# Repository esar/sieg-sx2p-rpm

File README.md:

# sieg-sx2p-rpm
SIEG SX2P Mini Mill RPM and Feed Display

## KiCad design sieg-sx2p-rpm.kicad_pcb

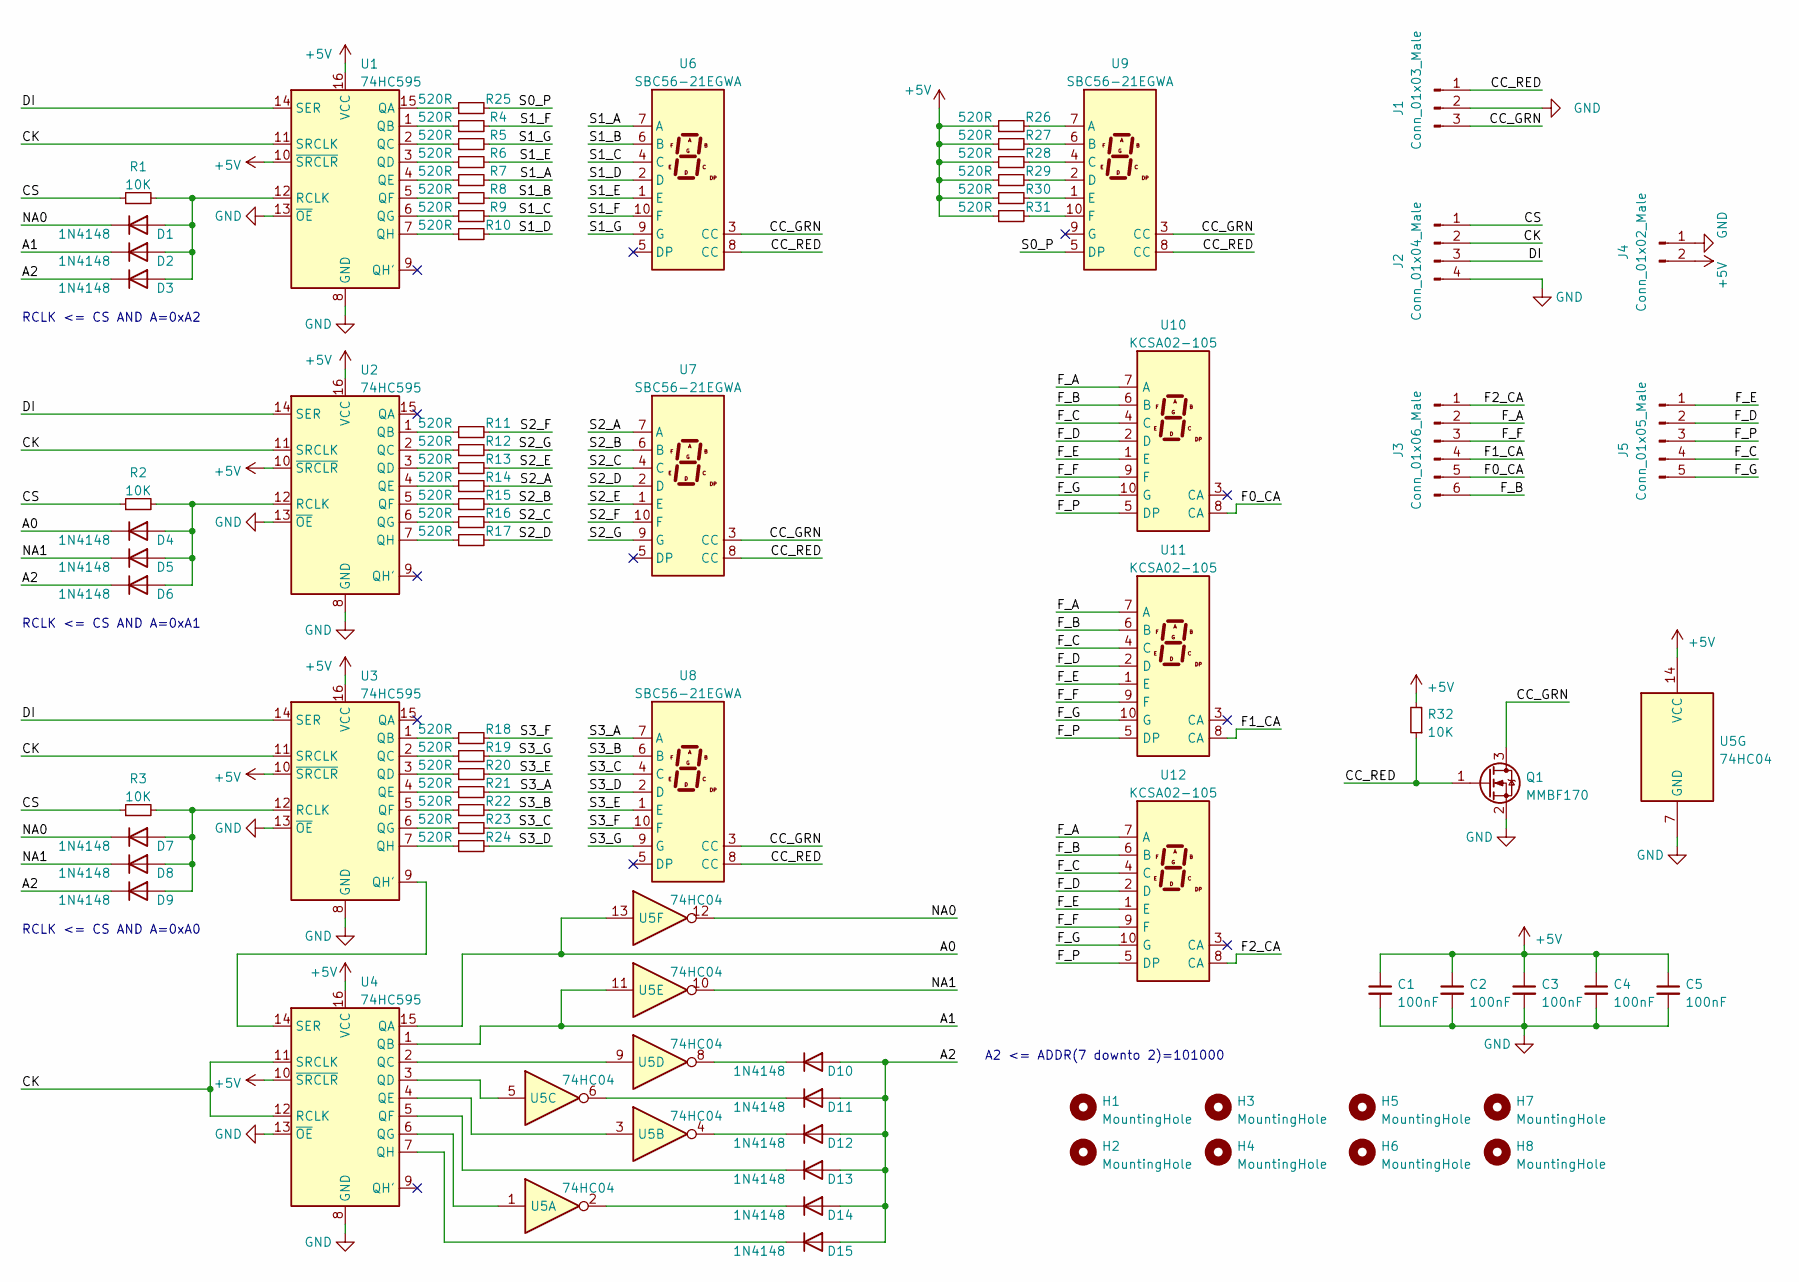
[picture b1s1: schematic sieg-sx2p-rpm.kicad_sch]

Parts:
C1, C2, C3, C4, C5: 100nF; C_0603_1608Metric
D1, D2, D3, D4, D5, D6, D7, D8, D9, D10, D11, D12, D13, D14, D15: 1N4148; D_SOD-323
H1, H2, H3, H4, H5, H6, H7, H8: MountingHole; MountingHole_3mm
J1: Conn_01x03_Male; JST_XH_B3B-XH-A_1x03_P2.50mm_Vertical
J2: Conn_01x04_Male; JST_XH_B4B-XH-A_1x04_P2.50mm_Vertical
J3: Conn_01x06_Male; JST_XH_B6B-XH-A_1x06_P2.50mm_Vertical
J4: Conn_01x02_Male; JST_XH_B2B-XH-A_1x02_P2.50mm_Vertical
J5: Conn_01x05_Male; JST_XH_B5B-XH-A_1x05_P2.50mm_Vertical
Q1: MMBF170; SOT-23
R1, R2, R3, R32: 10K; R_0603_1608Metric
R4, R5, R6, R7, R8, R9, R10, R11, R12, R13, R14, R15, R16, R17, R18, R19, R20, R21, R22, R23, R24, R25, R26, R27, R28, R29, R30, R31: 520R; R_0603_1608Metric
U1, U2, U3, U4: 74HC595; DIP-16_W7.62mm
U5: 74HC04; DIP-14_W7.62mm
U6, U7, U8, U9: SBC56-21EGWA; D1X8K
U10, U11, U12: KCSA02-105; D1X8K

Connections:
+5V: C1.1, C2.1, C3.1, C4.1, C5.1, J4.2, R26.1, R27.1, R28.1, R29.1, R30.1, R31.1, R32.2, U1.10 (~SRCLR), U1.16 (VCC), U2.10 (~SRCLR), U2.16 (VCC), U3.10 (~SRCLR), U3.16 (VCC), U4.10 (~SRCLR), U4.16 (VCC), U5.14 (VCC)
/A0: D4.1 (K), U4.15 (QA), U5.13
/A1: D2.1 (K), U4.1 (QB), U5.11
/A2: D3.1 (K), D6.1 (K), D9.1 (K), D10.2 (A), D11.2 (A), D12.2 (A), D13.2 (A), D14.2 (A), D15.2 (A)
/CC_GRN: J1.3, Q1.3 (D), U6.3 (CC), U7.3 (CC), U8.3 (CC), U9.3 (CC)
/CC_RED: J1.1, Q1.1 (G), R32.1, U6.8 (CC), U7.8 (CC), U8.8 (CC), U9.8 (CC)
/CK: J2.2, U1.11 (SRCLK), U2.11 (SRCLK), U3.11 (SRCLK), U4.11 (SRCLK), U4.12 (RCLK)
/CS: J2.1, R1.1, R2.1, R3.1
/DI: J2.3, U1.14 (SER), U2.14 (SER), U3.14 (SER)
/F0_CA: J3.5, U10.8 (CA)
/F1_CA: J3.4, U11.8 (CA)
/F2_CA: J3.1, U12.8 (CA)
/F_A: J3.2, U10.7 (A), U11.7 (A), U12.7 (A)
/F_B: J3.6, U10.6 (B), U11.6 (B), U12.6 (B)
/F_C: J5.4, U10.4 (C), U11.4 (C), U12.4 (C)
/F_D: J5.2, U10.2 (D), U11.2 (D), U12.2 (D)
/F_E: J5.1, U10.1 (E), U11.1 (E), U12.1 (E)
/F_F: J3.3, U10.9 (F), U11.9 (F), U12.9 (F)
/F_G: J5.5, U10.10 (G), U11.10 (G), U12.10 (G)
/F_P: J5.3, U10.5 (DP), U11.5 (DP), U12.5 (DP)
/NA0: D1.1 (K), D7.1 (K), U5.12
/NA1: D5.1 (K), D8.1 (K), U5.10
/S0_P: R25.2, U9.5 (DP)
/S1_A: R7.2, U6.7 (A)
/S1_B: R8.2, U6.6 (B)
/S1_C: R9.2, U6.4 (C)
/S1_D: R10.2, U6.2 (D)
/S1_E: R6.2, U6.1 (E)
/S1_F: R4.2, U6.10 (F)
/S1_G: R5.2, U6.9 (G)
/S2_A: R14.2, U7.7 (A)
/S2_B: R15.2, U7.6 (B)
/S2_C: R16.2, U7.4 (C)
/S2_D: R17.2, U7.2 (D)
/S2_E: R13.2, U7.1 (E)
/S2_F: R11.2, U7.10 (F)
/S2_G: R12.2, U7.9 (G)
/S3_A: R21.2, U8.7 (A)
/S3_B: R22.2, U8.6 (B)
/S3_C: R23.2, U8.4 (C)
/S3_D: R24.2, U8.2 (D)
/S3_E: R20.2, U8.1 (E)
/S3_F: R18.2, U8.10 (F)
/S3_G: R19.2, U8.9 (G)
GND: C1.2, C2.2, C3.2, C4.2, C5.2, J1.2, J2.4, J4.1, Q1.2 (S), U1.8 (GND), U1.13 (~OE), U2.8 (GND), U2.13 (~OE), U3.8 (GND), U3.13 (~OE), U4.8 (GND), U4.13 (~OE), U5.7 (GND)
unnamed: D1.2 (A), D2.2 (A), D3.2 (A), R1.2, U1.12 (RCLK)
unnamed: D4.2 (A), D5.2 (A), D6.2 (A), R2.2, U2.12 (RCLK)
unnamed: D7.2 (A), D8.2 (A), D9.2 (A), R3.2, U3.12 (RCLK)
unnamed: D10.1 (K), U5.8
unnamed: D11.1 (K), U5.6
unnamed: D12.1 (K), U5.4
unnamed: D13.1 (K), U4.5 (QF)
unnamed: D14.1 (K), U5.2
unnamed: D15.1 (K), U4.7 (QH)
unnamed: R4.1, U1.1 (QB)
unnamed: R5.1, U1.2 (QC)
unnamed: R6.1, U1.3 (QD)
unnamed: R7.1, U1.4 (QE)
unnamed: R8.1, U1.5 (QF)
unnamed: R9.1, U1.6 (QG)
unnamed: R10.1, U1.7 (QH)
unnamed: R11.1, U2.1 (QB)
unnamed: R12.1, U2.2 (QC)
unnamed: R13.1, U2.3 (QD)
unnamed: R14.1, U2.4 (QE)
unnamed: R15.1, U2.5 (QF)
unnamed: R16.1, U2.6 (QG)
unnamed: R17.1, U2.7 (QH)
unnamed: R18.1, U3.1 (QB)
unnamed: R19.1, U3.2 (QC)
unnamed: R20.1, U3.3 (QD)
unnamed: R21.1, U3.4 (QE)
unnamed: R22.1, U3.5 (QF)
unnamed: R23.1, U3.6 (QG)
unnamed: R24.1, U3.7 (QH)
unnamed: R25.1, U1.15 (QA)
unnamed: R26.2, U9.7 (A)
unnamed: R27.2, U9.6 (B)
unnamed: R28.2, U9.4 (C)
unnamed: R29.2, U9.2 (D)
unnamed: R30.2, U9.1 (E)
unnamed: R31.2, U9.10 (F)
unnamed: U3.9 (QH'), U4.14 (SER)
unnamed: U4.2 (QC), U5.9
unnamed: U4.3 (QD), U5.5
unnamed: U4.4 (QE), U5.3
unnamed: U4.6 (QG), U5.1

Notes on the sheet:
RCLK <= CS AND A=0xA0
RCLK <= CS AND A=0xA2
RCLK <= CS AND A=0xA1
A2 <= ADDR(7 downto 2)=101000

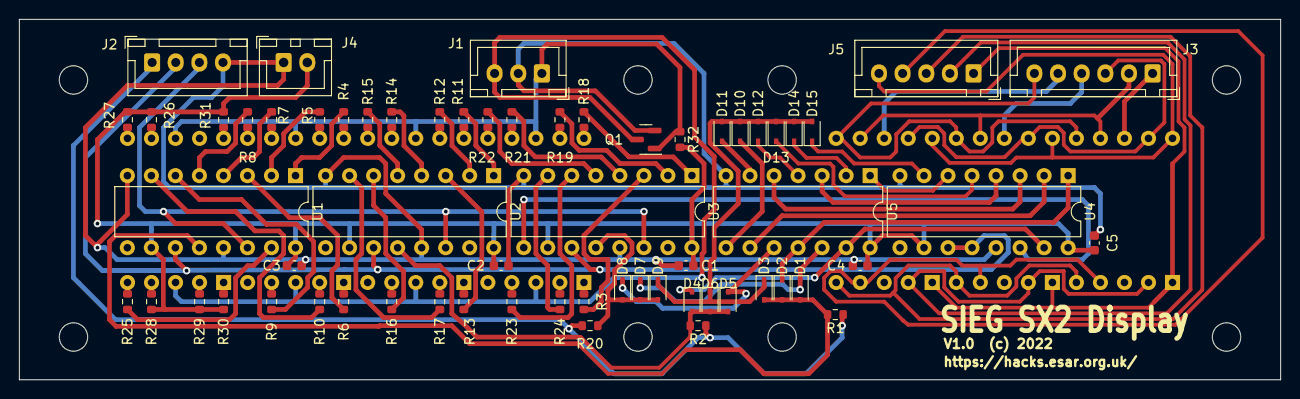
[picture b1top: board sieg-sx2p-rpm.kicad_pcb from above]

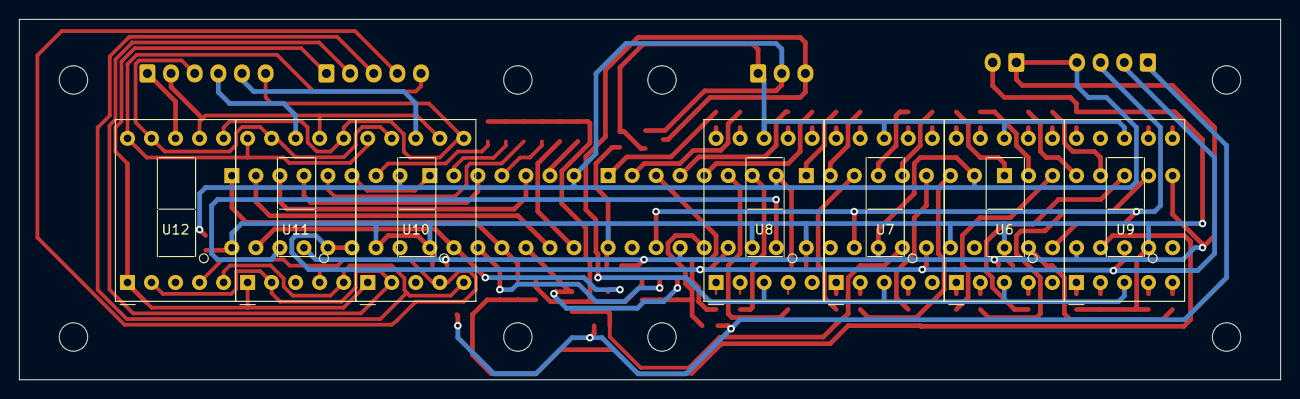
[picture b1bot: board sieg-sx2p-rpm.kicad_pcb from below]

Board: 2 copper layers, 133.3 x 38.1 mm, 78 parts (7 on the bottom side), 87 nets.

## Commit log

2023-04-07 SIEG SX2P RPM / feed display
2023-06-18 add image of finished project

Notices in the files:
sieg-sx2p-rpm.kicad_pcb:
V1.0  (c) 2022
